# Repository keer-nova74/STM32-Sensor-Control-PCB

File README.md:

# STM32 Sensor & Control PCB

## Project Overview

A compact, microcontroller-based PCB design concept intended for embedded sensing, peripheral interfacing, and control applications. The proposed board uses an STM32 microcontroller as the central controller, with dedicated interfaces for sensors, communication, and user interaction.

The design focuses on a modular hardware architecture that supports straightforward peripheral connectivity, debugging, and future expansion.

## Key Features

- **Microcontroller:** STM32-based control architecture
- **Sensor Interface:** I²C connectivity for external sensors
- **Communication:** UART interface for serial data exchange
- **User Interface:** Push button and status LEDs
- **Audio Indication:** Buzzer output
- **Power Management:** Regulated supply for controller and peripherals
- **Programming & Debugging:** Dedicated programming and debugging headers
- **PCB Layout:** Two-layer board architecture

## Hardware Architecture

The proposed design is organized into the following functional blocks:

1. **Controller Unit** – Coordinates sensor communication and peripheral control.
2. **Sensor Interface** – Provides an I²C connection for external sensing modules.
3. **Communication Interface** – Supports UART-based serial communication.
4. **User Interaction** – Uses a push button, LEDs, and a buzzer for input and status indication.
5. **Power Section** – Provides regulated power to the controller and connected peripherals.
6. **Debug Interface** – Provides access for programming and firmware debugging.

## PCB Design Approach

The planned design workflow includes:

- Defining component and interface requirements
- Creating the electronic schematic in KiCad
- Selecting suitable component footprints
- Arranging components according to functional blocks
- Routing signal and power connections across two copper layers
- Checking electrical connections and PCB design rules
- Preparing Gerber and drill outputs for manufacturing review

## Tools & Technologies

- KiCad
- STM32 microcontroller platform
- I²C and UART communication
- GPIO interfacing
- Two-layer PCB design principles

## Applications

- Embedded control systems
- Sensor-based monitoring
- Microcontroller prototyping
- Hardware-software integration

## Project Status

Design planning and documentation. Schematic development, PCB layout, electrical verification, and manufacturing output generation are pending.

## Future Improvements

- Complete the schematic and PCB layout
- Verify component footprints and electrical connections
- Perform design rule checks
- Generate manufacturing files
- Validate the board through hardware testing

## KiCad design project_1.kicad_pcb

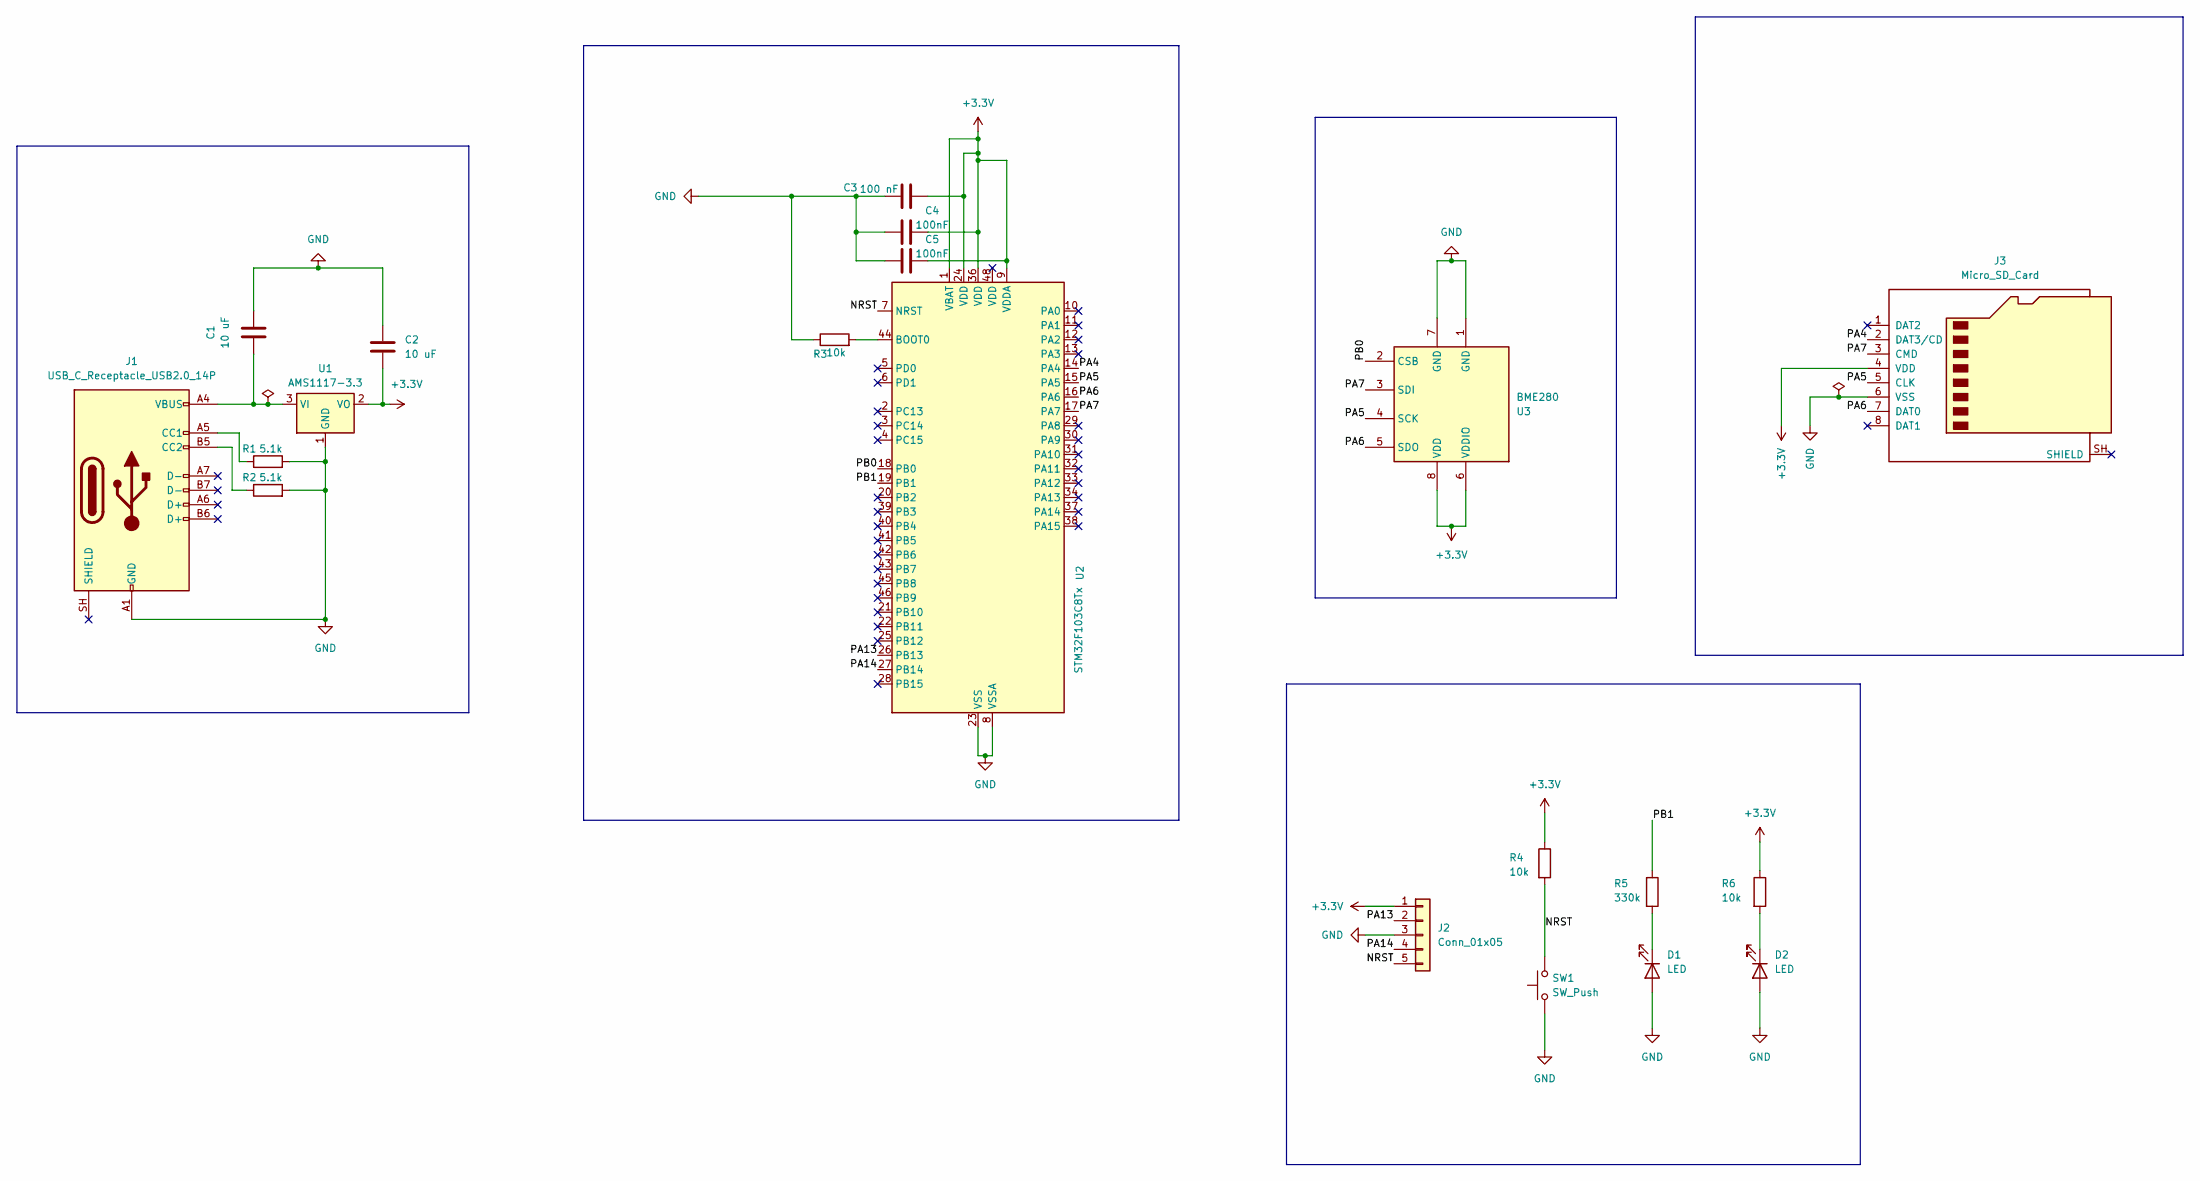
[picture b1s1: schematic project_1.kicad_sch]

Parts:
C1, C2: 10 uF; C_0805_2012Metric
C3: 100 nF; C_0805_2012Metric
C4, C5: 100nF; C_0805_2012Metric
D1, D2: LED; LED_0805_2012Metric
J1: USB_C_Receptacle_USB2.0_14P; USB_C_Receptacle_GCT_USB4105-xx-A_16P_TopMnt_Horizontal
J2: Conn_01x05; PinHeader_1x05_P2.54mm_Vertical
J3: Micro_SD_Card; microSD_HC_Hirose_DM3D-SF
R1, R2: 5.1k; R_0805_2012Metric
R3, R4: 10k; R_0805_2012Metric_Pad1.20x1.40mm_HandSolder
R5: 330k; R_Axial_DIN0309_L9.0mm_D3.2mm_P12.70mm_Horizontal
R6: 10k; R_Axial_DIN0309_L9.0mm_D3.2mm_P12.70mm_Horizontal
SW1: SW_Push; SW_PUSH_6mm
U1: AMS1117-3.3; SOT-223-3_TabPin2
U2: STM32F103C8Tx; LQFP-48_7x7mm_P0.5mm
U3: BME280; Bosch_LGA-8_2.5x2.5mm_P0.65mm_ClockwisePinNumbering

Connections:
+3.3V: C2.2, C3.2, C4.1, C5.1, J2.1, J3.4 (VDD), R4.1, R6.1, U1.2 (VO), U2.1 (VBAT), U2.9 (VDDA), U2.24 (VDD), U2.36 (VDD), U3.6 (VDDIO), U3.8 (VDD)
/NRST: J2.5, R4.2, SW1.2, U2.7 (NRST)
/PA4: J3.2 (DAT3/CD), U2.14 (PA4)
/PA5: J3.5 (CLK), U2.15 (PA5), U3.4 (SCK)
/PA6: J3.7 (DAT0), U2.16 (PA6), U3.5 (SDO)
/PA7: J3.3 (CMD), U2.17 (PA7), U3.3 (SDI)
/PA13: J2.2, U2.26 (PB13)
/PA14: J2.4, U2.27 (PB14)
/PB0: U2.18 (PB0), U3.2 (CSB)
/PB1: R5.1, U2.19 (PB1)
GND: C1.2, C2.1, C3.1, C4.2, C5.2, D1.2 (A), D2.2 (A), J1.A1 (GND), J1.A12 (GND), J1.B1 (GND), J1.B12 (GND), J2.3, J3.6 (VSS), R1.2, R2.2, R3.1, SW1.1, U1.1 (GND), U2.8 (VSSA), U2.23 (VSS), U2.35 (VSS), U2.47 (VSS), U3.1 (GND), U3.7 (GND)
unnamed: D1.1 (K), R5.2
unnamed: D2.1 (K), R6.2
unnamed: J1.A5 (CC1), R1.1
unnamed: J1.B5 (CC2), R2.1
unnamed: C1.1, J1.A4 (VBUS), J1.A9 (VBUS), J1.B4 (VBUS), J1.B9 (VBUS), U1.3 (VI)
unnamed: R3.2, U2.44 (BOOT0)

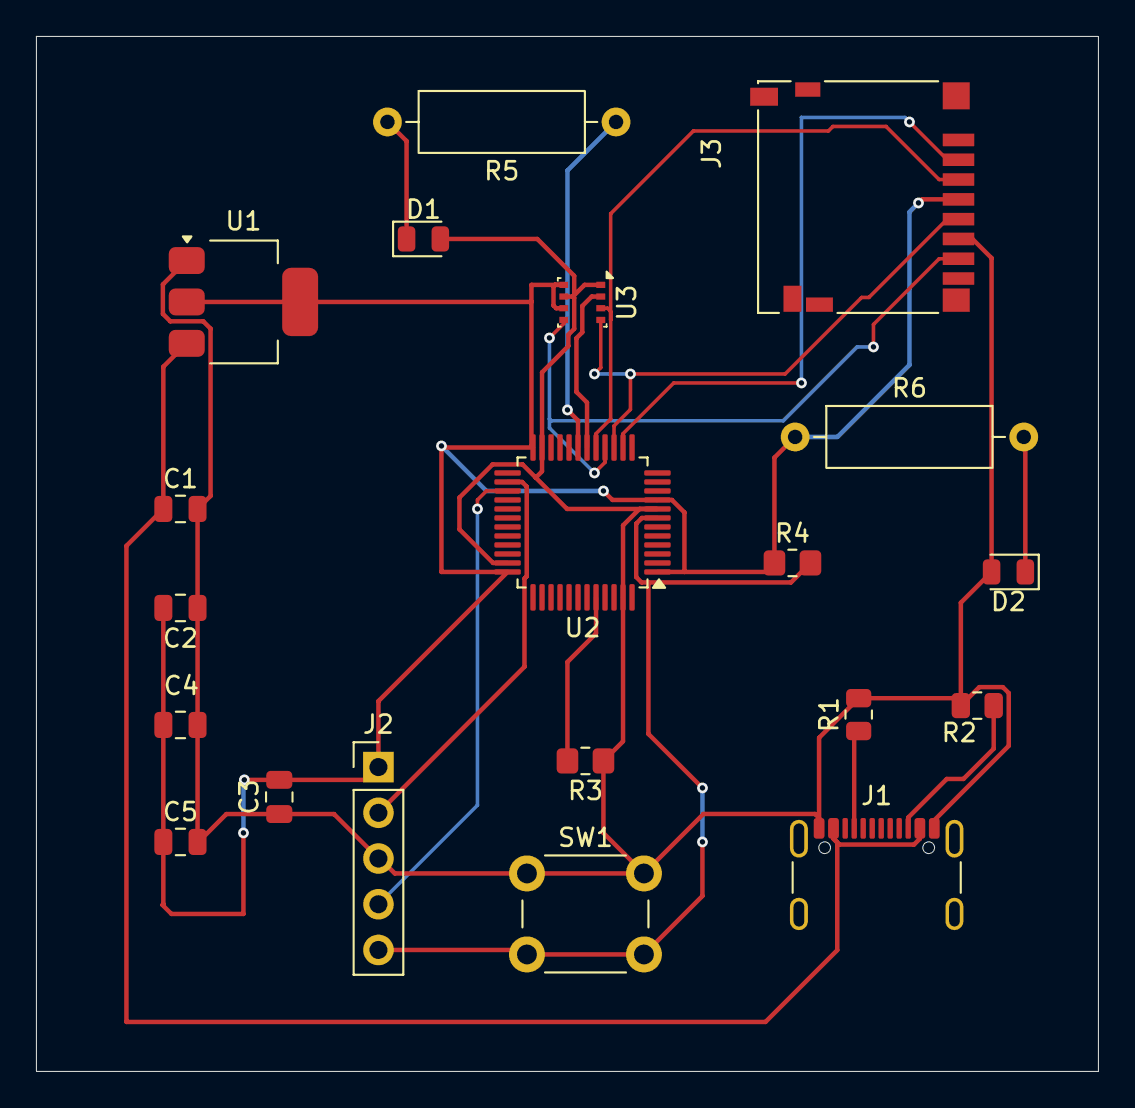
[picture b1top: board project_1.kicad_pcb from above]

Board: 2 copper layers, 59.0 x 57.5 mm, 20 parts (0 on the bottom side), 17 nets.
